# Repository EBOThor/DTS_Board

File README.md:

# DTS_Board
 Digital to Synchro board

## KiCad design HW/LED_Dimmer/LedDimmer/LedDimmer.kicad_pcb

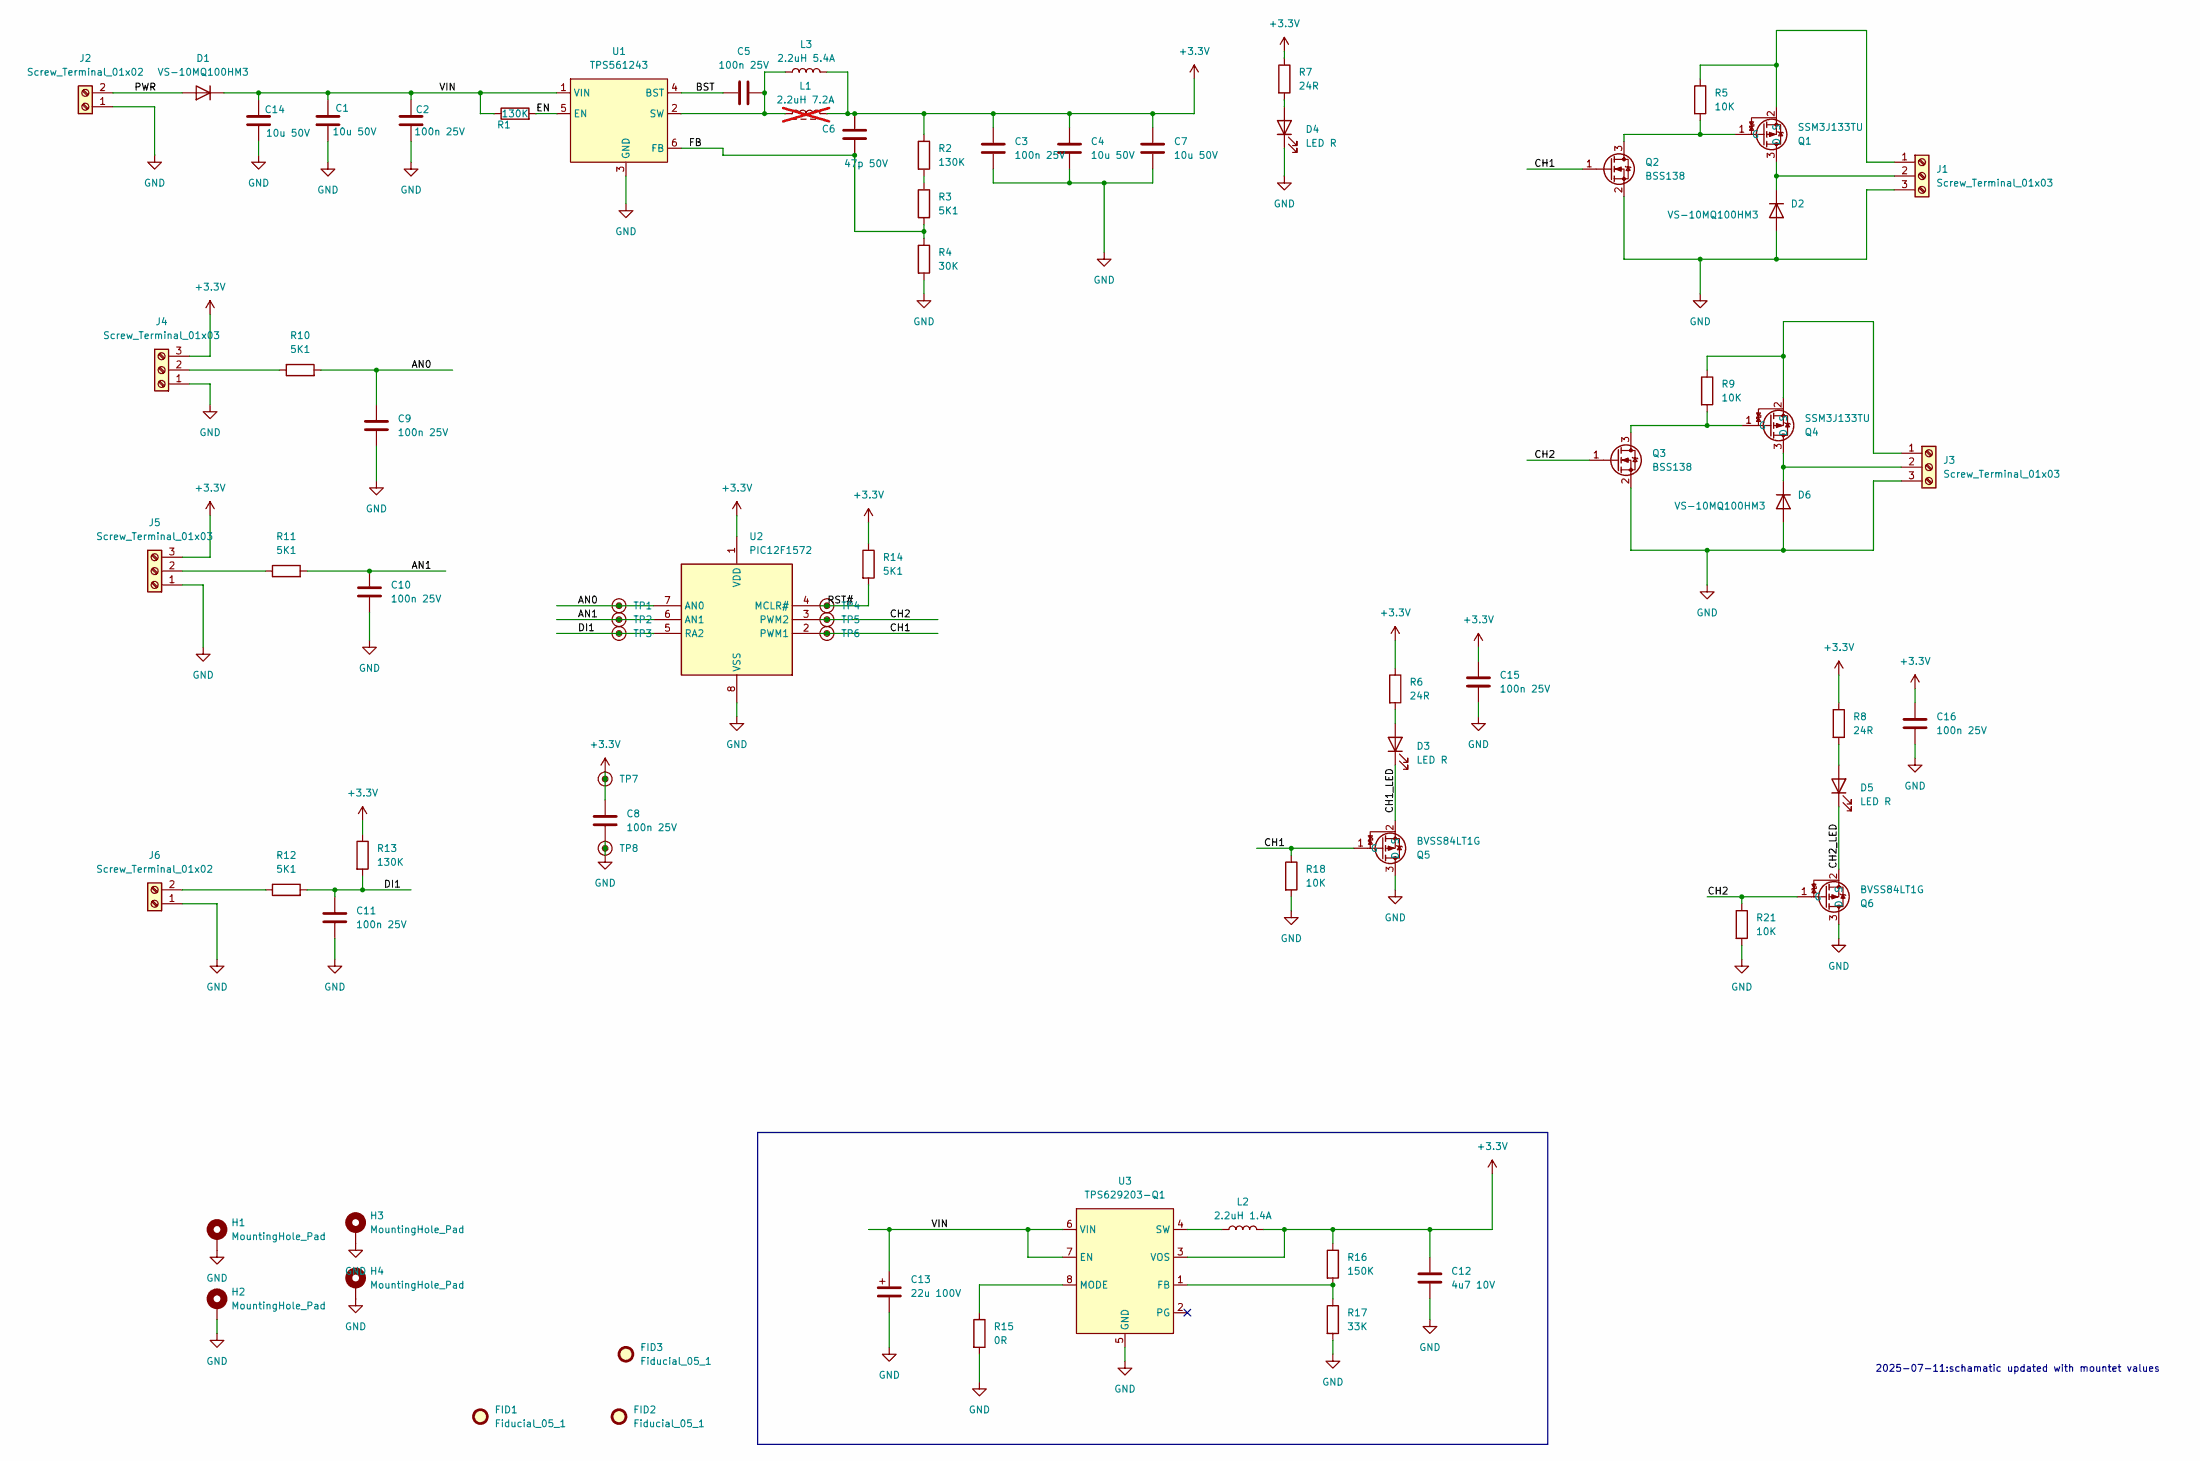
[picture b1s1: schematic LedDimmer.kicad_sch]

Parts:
C1, C14: 10u 50V; C_0805_2012Metric; MPN GRM21BR61H106KE43L
C2, C3, C5, C8, C9, C10, C11, C15, C16: 100n 25V; C_0603_1608Metric; MPN C;M;100n;10p;25V;S;0603
C4, C7: 10u 50V; C_0603_1608Metric; MPN C;M;10u;10p;50V;S;0603
C6: 47p 50V; C_0603_1608Metric; MPN C;C;T1;S;P0603;NA
C12: 4u7 10V; C_0603_1608Metric; MPN C;C;T1;S;P0603;NA
C13: 22u 100V; CP_Elec_8x10.5; MPN WE 865060853003
D1, D2, D6: VS-10MQ100HM3; D_SMA; MPN VS-10MQ100HM3/5AT
D3, D4, D5: LED R; LED_0603_1608Metric; MPN D;LED;R;3V;25mA
FID1, FID2, FID3: Fiducial_05_1; Fiducial_0.5mm_Mask1mm
H1, H2, H3, H4: MountingHole_Pad; MountingHole_2.2mm_M2_DIN965_Pad_TopBottom
J1, J3, J4, J5: Screw_Terminal_01x03; PinHeader_1x03_P2.54mm_Vertical
J2, J6: Screw_Terminal_01x02; PinHeader_1x02_P2.54mm_Vertical
L1: 2.2uH 7.2A; L_Bourns_bt_SRR1050HA; MPN SRR1050HA-2R2Y; not fitted
L2: 2.2uH 1.4A; L_0806_2016Metric; MPN DFE201612E-2R2M=P2
L3: 2.2uH 5.4A; L_1210_3225Metric; MPN IHLP1210BZEZ2R2M5A
Q1, Q4: SSM3J133TU; SOT-323_SC-70; MPN SSM3J133TU,LF
Q2, Q3: BSS138; SOT-23; MPN BSS138
Q5, Q6: BVSS84LT1G; SOT-23; MPN BVSS84LT1G
R1, R2, R13: 130K; R_0603_1608Metric; MPN R;G;T1;S;P0603;NA
R3, R10, R11, R12, R14: 5K1; R_0603_1608Metric; MPN R;G;5K1;S;P0603;NA
R4: 30K; R_0603_1608Metric; MPN R;G;T1;S;P0603;NA
R5, R9, R18, R21: 10K; R_0603_1608Metric; MPN R;G;10K;10P0;S;0603
R6, R7, R8: 24R; R_0603_1608Metric; MPN R;G;T1;S;P0603;NA
R15: 0R; R_0603_1608Metric; MPN R;G;0R;10P0;S;0603
R16: 150K; R_0603_1608Metric; MPN R;G;T1;S;P0603;NA
R17: 33K; R_0603_1608Metric; MPN R;G;T1;S;P0603;NA
TP1, TP2, TP3, TP4, TP5, TP6, TP7, TP8: TestPoint; TestPoint_THTPad_D1.0mm_Drill0.5mm
U1: TPS561243; SOT-563; MPN TPS561243DRLR
U2: PIC12F1572; SOIC-8_3.9x4.9mm_P1.27mm; MPN PIC12F1572-I/SN
U3: TPS629203-Q1; SOT-583-8; MPN TPS629203QDRLR

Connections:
+3.3V: C3.2, C4.1, C6.1, C7.1, C8.2, C12.1, C15.2, C16.2, J4.3, J5.3, L1.2, L2.2, L3.2, R2.1, R6.1, R7.1, R8.1, R13.1, R14.1, R16.1, TP7.1, U2.1 (VDD), U3.3 (VOS)
/AN0: C9.2, R10.2, TP1.1, U2.7 (AN0)
/AN1: C10.2, R11.2, TP2.1, U2.6 (AN1)
/BST: C5.1, U1.4 (BST)
/CH1: Q2.1 (G), Q5.1 (G), R18.1, TP6.1, U2.2 (PWM1)
/CH1_LED: D3.1 (K), Q5.2 (S)
/CH2: Q3.1 (G), Q6.1 (G), R21.1, TP5.1, U2.3 (PWM2)
/CH2_LED: D5.1 (K), Q6.2 (S)
/DI1: C11.2, R12.2, R13.2, TP3.1, U2.5 (RA2)
/EN: R1.2, U1.5 (EN)
/FB: C6.2, R3.2, R4.1, U1.6 (FB)
/PWR: D1.2 (A), J2.2
/RST#: R14.2, TP4.1, U2.4 (MCLR#)
/VIN: C1.1, C2.2, C13.1, C14.1, D1.1 (K), R1.1, U1.1 (VIN), U3.6 (VIN), U3.7 (EN)
GND: C1.2, C2.1, C3.1, C4.2, C7.2, C8.1, C9.1, C10.1, C11.1, C12.2, C13.2, C14.2, C15.1, C16.1, D2.2 (A), D4.1 (K), D6.2 (A), H1.1, H2.1, H3.1, H4.1, J1.3, J2.1, J3.3, J4.1, J5.1, J6.1, Q2.2 (S), Q3.2 (S), Q5.3 (D), Q6.3 (D), R4.2, R15.2, R17.2, R18.2, R21.2, TP8.1, U1.3 (GND), U2.8 (VSS), U3.5 (GND)
unnamed: D2.1 (K), J1.2, Q1.3 (D)
unnamed: D3.2 (A), R6.2
unnamed: D4.2 (A), R7.2
unnamed: D5.2 (A), R8.2
unnamed: D6.1 (K), J3.2, Q4.3 (D)
unnamed: J1.1, Q1.2 (S), R5.1
unnamed: J3.1, Q4.2 (S), R9.1
unnamed: J4.2, R10.1
unnamed: J5.2, R11.1
unnamed: J6.2, R12.1
unnamed: L2.1, U3.4 (SW)
unnamed: Q1.1 (G), Q2.3 (D), R5.2
unnamed: Q3.3 (D), Q4.1 (G), R9.2
unnamed: R2.2, R3.1
unnamed: R15.1, U3.8 (MODE)
unnamed: R16.2, R17.1, U3.1 (FB)
unnamed: C5.2, L1.1, L3.1, U1.2 (SW)

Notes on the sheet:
2025-07-11:schamatic updated with mountet values

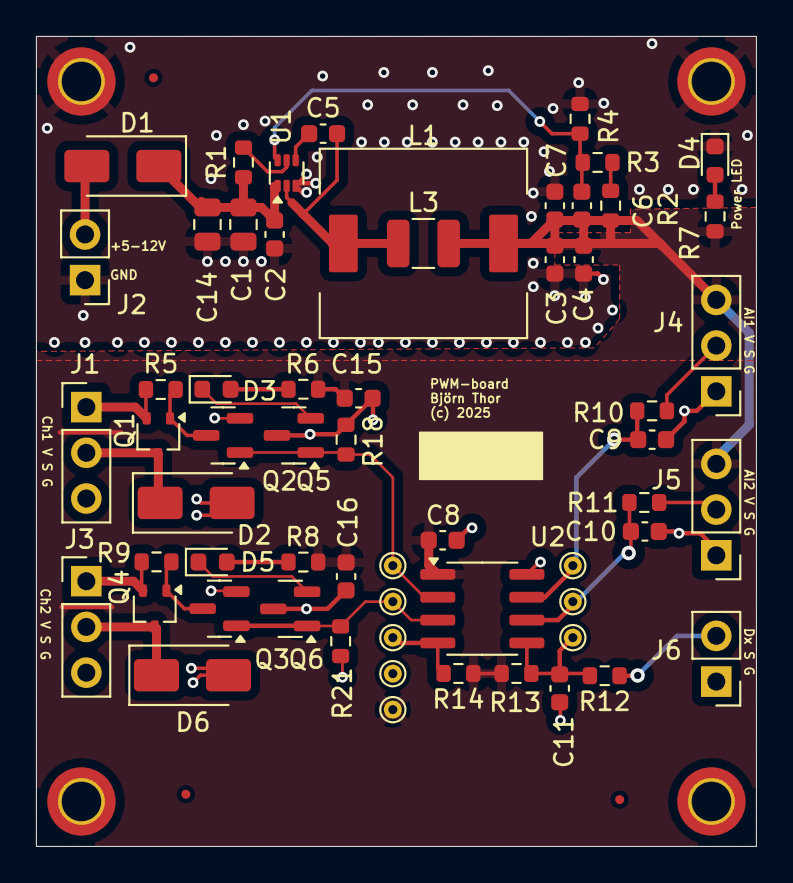
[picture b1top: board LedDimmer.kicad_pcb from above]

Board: 2 copper layers, 40.0 x 45.0 mm, 67 parts (0 on the bottom side), 29 nets.

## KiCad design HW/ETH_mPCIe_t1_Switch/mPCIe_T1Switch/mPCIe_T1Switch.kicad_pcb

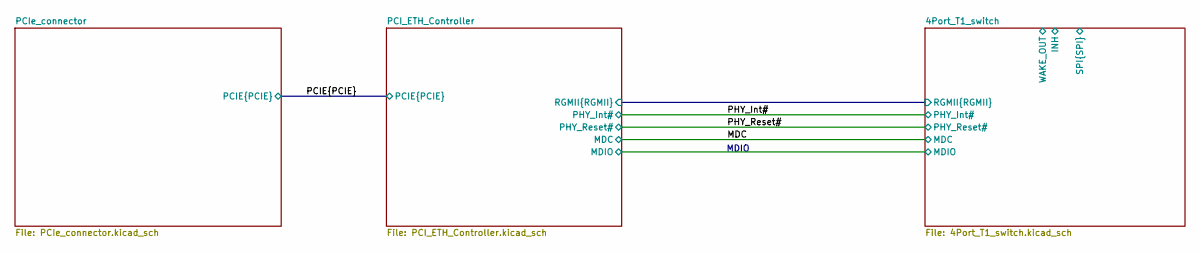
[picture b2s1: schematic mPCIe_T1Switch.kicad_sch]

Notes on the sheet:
MDIO

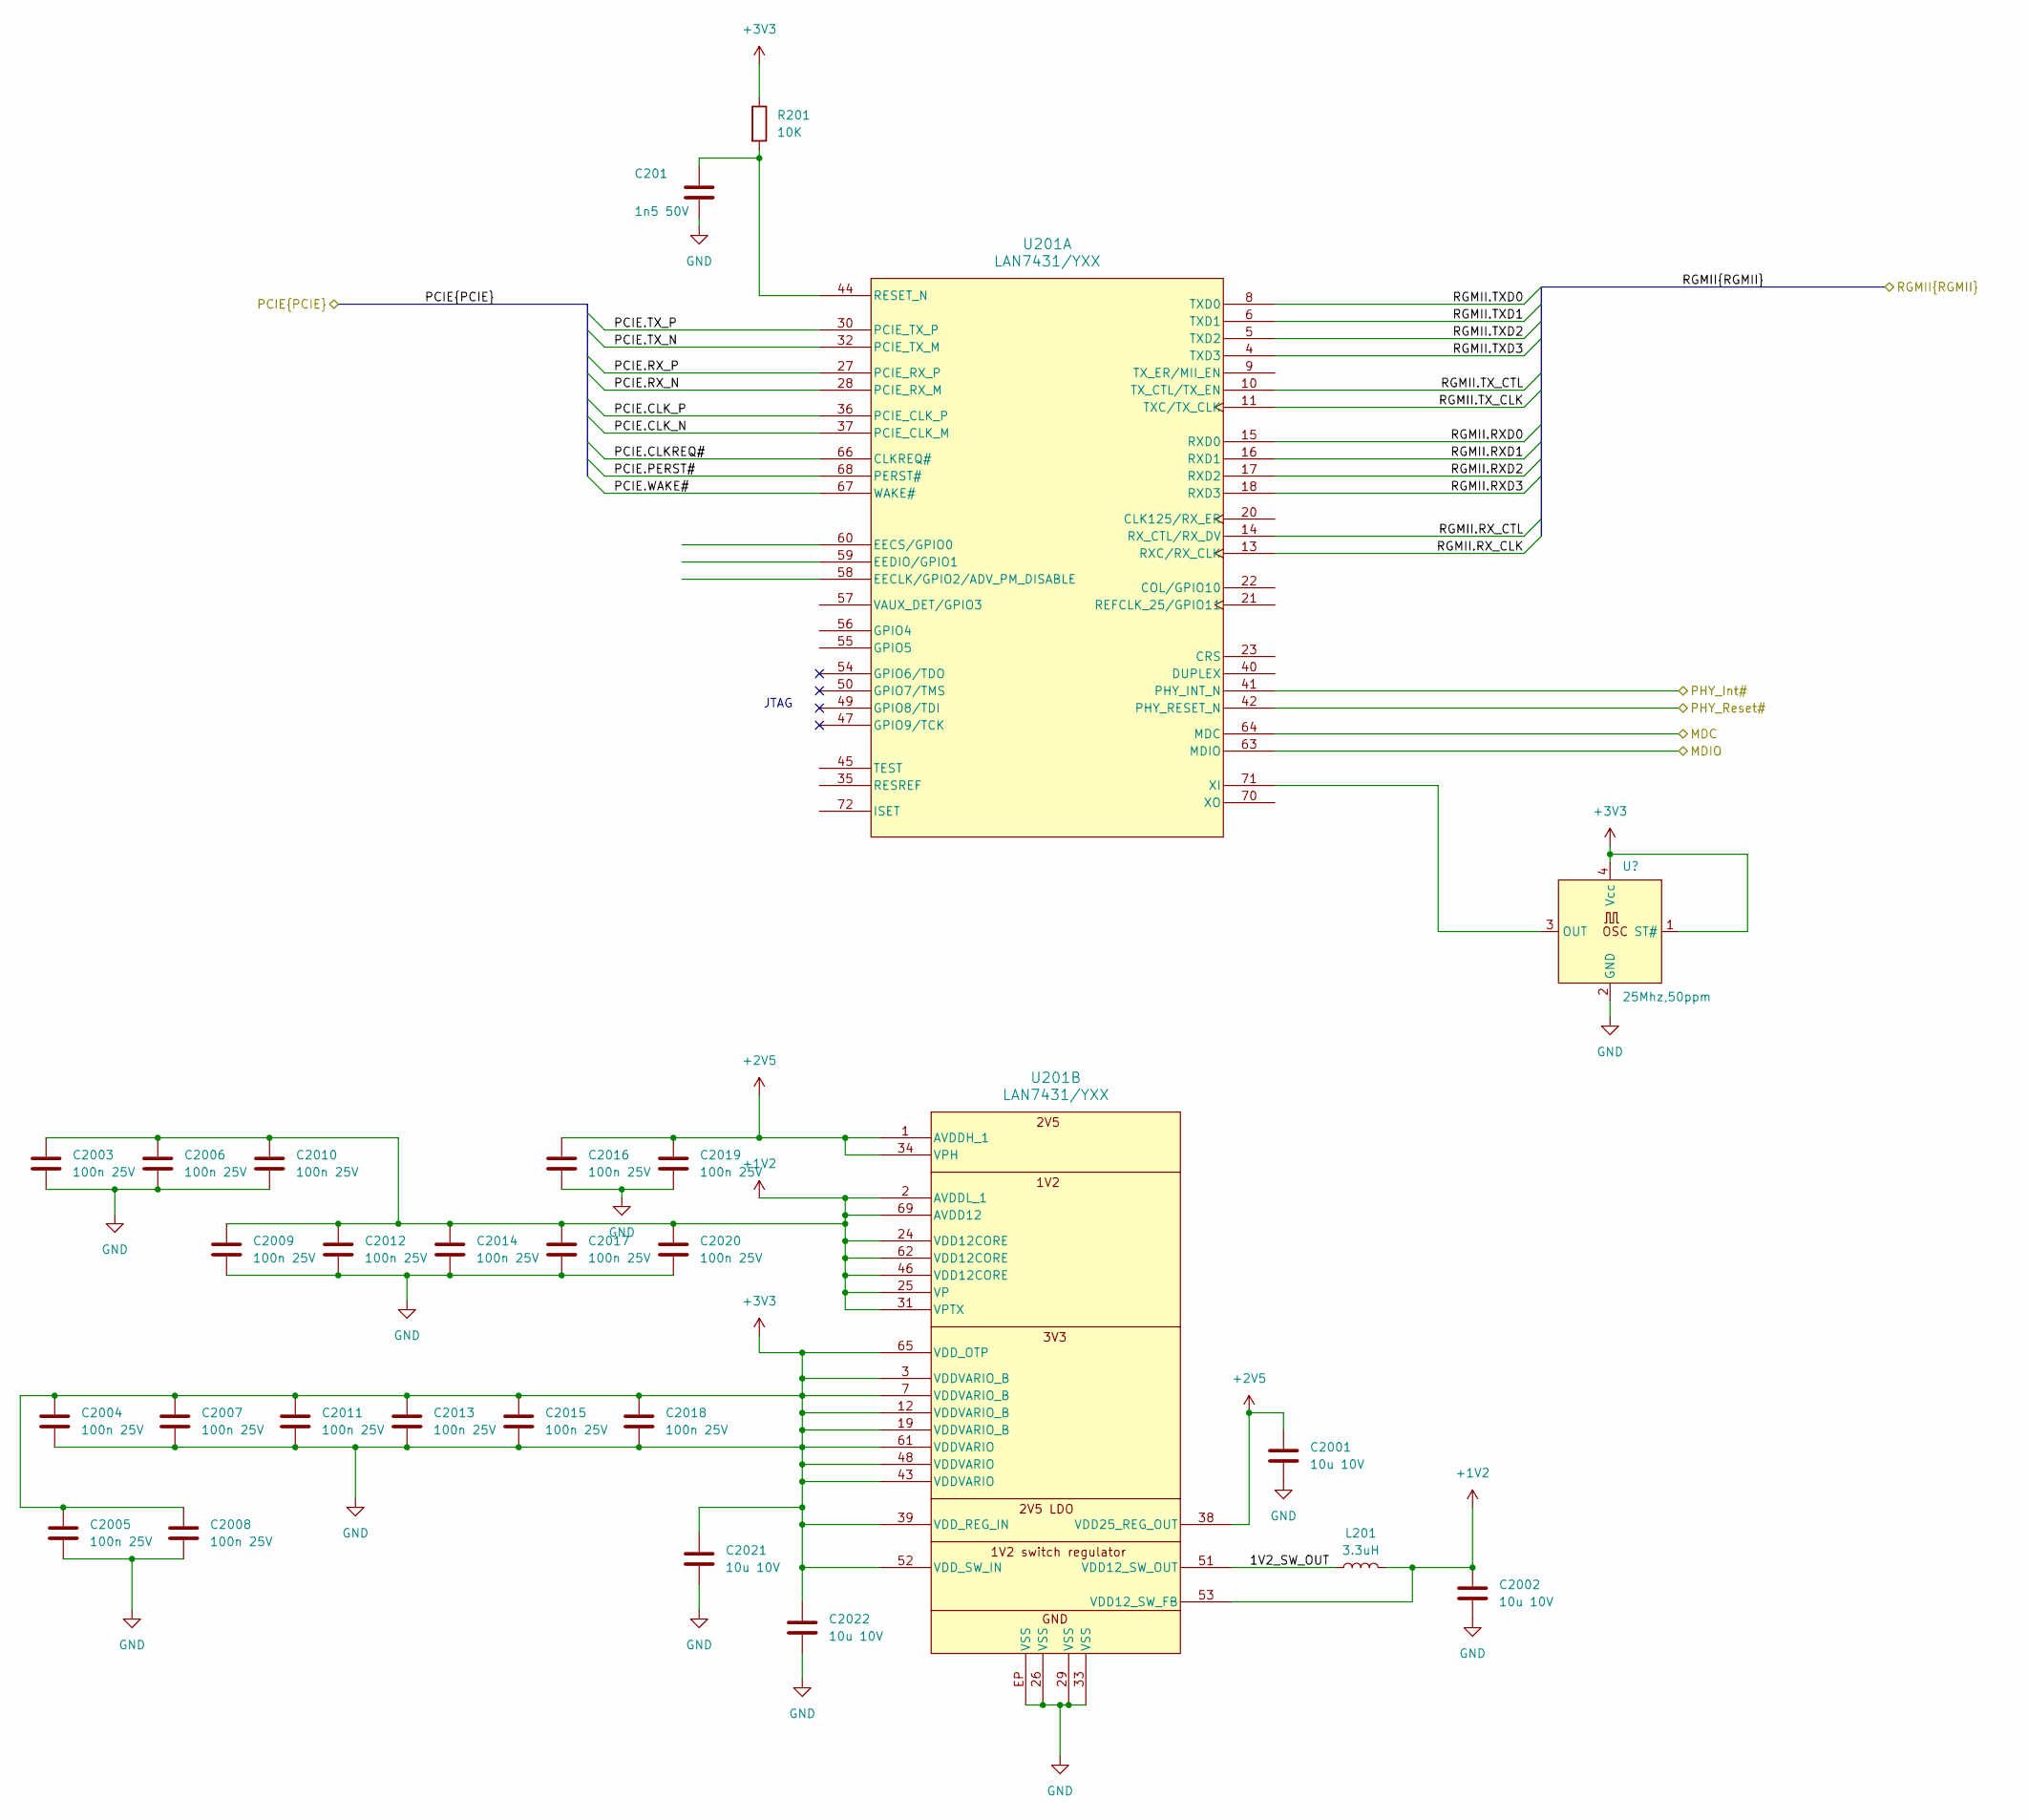
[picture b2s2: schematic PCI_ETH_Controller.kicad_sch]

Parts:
C201: 1n5 50V; C_0603_1608Metric; MPN C;C;T1;S;P0603;NA
C2001, C2002, C2021, C2022: 10u 10V; C_0603_1608Metric; MPN C;M;10u;10p;10V;S;0603
C2003, C2004, C2005, C2006, C2007, C2008, C2009, C2010, C2011, C2012, C2013, C2014, C2015, C2016, C2017, C2018, C2019, C2020: 100n 25V; C_0603_1608Metric; MPN C;M;100n;10p;25V;S;0603
L201: 3.3uH; L_0806_2016Metric; MPN SRP2010DPA-3R3M
R201: 10K; R_0603_1608Metric; MPN R;G;10K;10P0;S;0603
U201: LAN7431/YXX; SQFN72_YXX_MCH; MPN LAN7431

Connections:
+1V2: C2002.1, C2003.1, C2006.1, C2009.1, C2010.1, C2012.1, C2014.1, C2017.1, C2020.1, L201.2, U201.2 (AVDDL_1), U201.24 (VDD12CORE), U201.25 (VP), U201.31 (VPTX), U201.46 (VDD12CORE), U201.53 (VDD12_SW_FB), U201.62 (VDD12CORE), U201.69 (AVDD12)
+2V5: C2001.1, C2016.1, C2019.1, U201.1 (AVDDH_1), U201.34 (VPH), U201.38 (VDD25_REG_OUT)
+3V3: C201.2, C2001.2, C2002.2, C2003.2, C2004.1, C2004.2, C2005.1, C2005.2, C2006.2, C2007.1, C2007.2, C2008.1, C2008.2, C2009.2, C2010.2, C2011.1, C2011.2, C2012.2, C2013.1, C2013.2, C2014.2, C2015.1, C2015.2, C2016.2, C2017.2, C2018.1, C2018.2, C2019.2, C2020.2, C2021.1, C2021.2, C2022.1, C2022.2, R201.1, U201.3 (VDDVARIO_B), U201.7 (VDDVARIO_B), U201.12 (VDDVARIO_B), U201.19 (VDDVARIO_B), U201.26 (VSS), U201.29 (VSS), U201.33 (VSS), U201.39 (VDD_REG_IN), U201.43 (VDDVARIO), U201.48 (VDDVARIO), U201.52 (VDD_SW_IN), U201.61 (VDDVARIO), U201.65 (VDD_OTP), U201.EP (VSS); also elsewhere on the board
/4Port_T1_switch/MDIO: U201.63 (MDIO); also elsewhere on the board
/4Port_T1_switch/RGMII.RXD0: U201.15 (RXD0); also elsewhere on the board
/4Port_T1_switch/RGMII.RXD1: U201.16 (RXD1); also elsewhere on the board
/4Port_T1_switch/RGMII.RXD2: U201.17 (RXD2); also elsewhere on the board
/4Port_T1_switch/RGMII.RXD3: U201.18 (RXD3); also elsewhere on the board
/4Port_T1_switch/RGMII.RX_CLK: U201.13 (RXC/RX_CLK); also elsewhere on the board
/4Port_T1_switch/RGMII.RX_CTL: U201.14 (RX_CTL/RX_DV); also elsewhere on the board
/4Port_T1_switch/RGMII.TXD0: U201.8 (TXD0); also elsewhere on the board
/4Port_T1_switch/RGMII.TXD1: U201.6 (TXD1); also elsewhere on the board
/4Port_T1_switch/RGMII.TXD2: U201.5 (TXD2); also elsewhere on the board
/4Port_T1_switch/RGMII.TXD3: U201.4 (TXD3); also elsewhere on the board
/4Port_T1_switch/RGMII.TX_CLK: U201.11 (TXC/TX_CLK); also elsewhere on the board
/4Port_T1_switch/RGMII.TX_CTL: U201.10 (TX_CTL/TX_EN); also elsewhere on the board
/MDC: U201.64 (MDC); also elsewhere on the board
/PCIE.CLKREQ#: U201.66 (CLKREQ#); also elsewhere on the board
/PCIE.CLK_N: U201.37 (PCIE_CLK_M); also elsewhere on the board
/PCIE.CLK_P: U201.36 (PCIE_CLK_P); also elsewhere on the board
/PCIE.PERST#: U201.68 (PERST#); also elsewhere on the board
/PCIE.RX_N: U201.28 (PCIE_RX_M); also elsewhere on the board
/PCIE.RX_P: U201.27 (PCIE_RX_P); also elsewhere on the board
/PCIE.TX_N: U201.32 (PCIE_TX_M); also elsewhere on the board
/PCIE.TX_P: U201.30 (PCIE_TX_P); also elsewhere on the board
/PCIE.WAKE#: U201.67 (WAKE#); also elsewhere on the board
/PCI_ETH_Controller/1V2_SW_OUT: L201.1, U201.51 (VDD12_SW_OUT)
/PHY_Int#: U201.41 (PHY_INT_N); also elsewhere on the board
/PHY_Reset#: U201.42 (PHY_RESET_N); also elsewhere on the board
unnamed: C201.1, R201.2, U201.44 (RESET_N)

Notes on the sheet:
JTAG

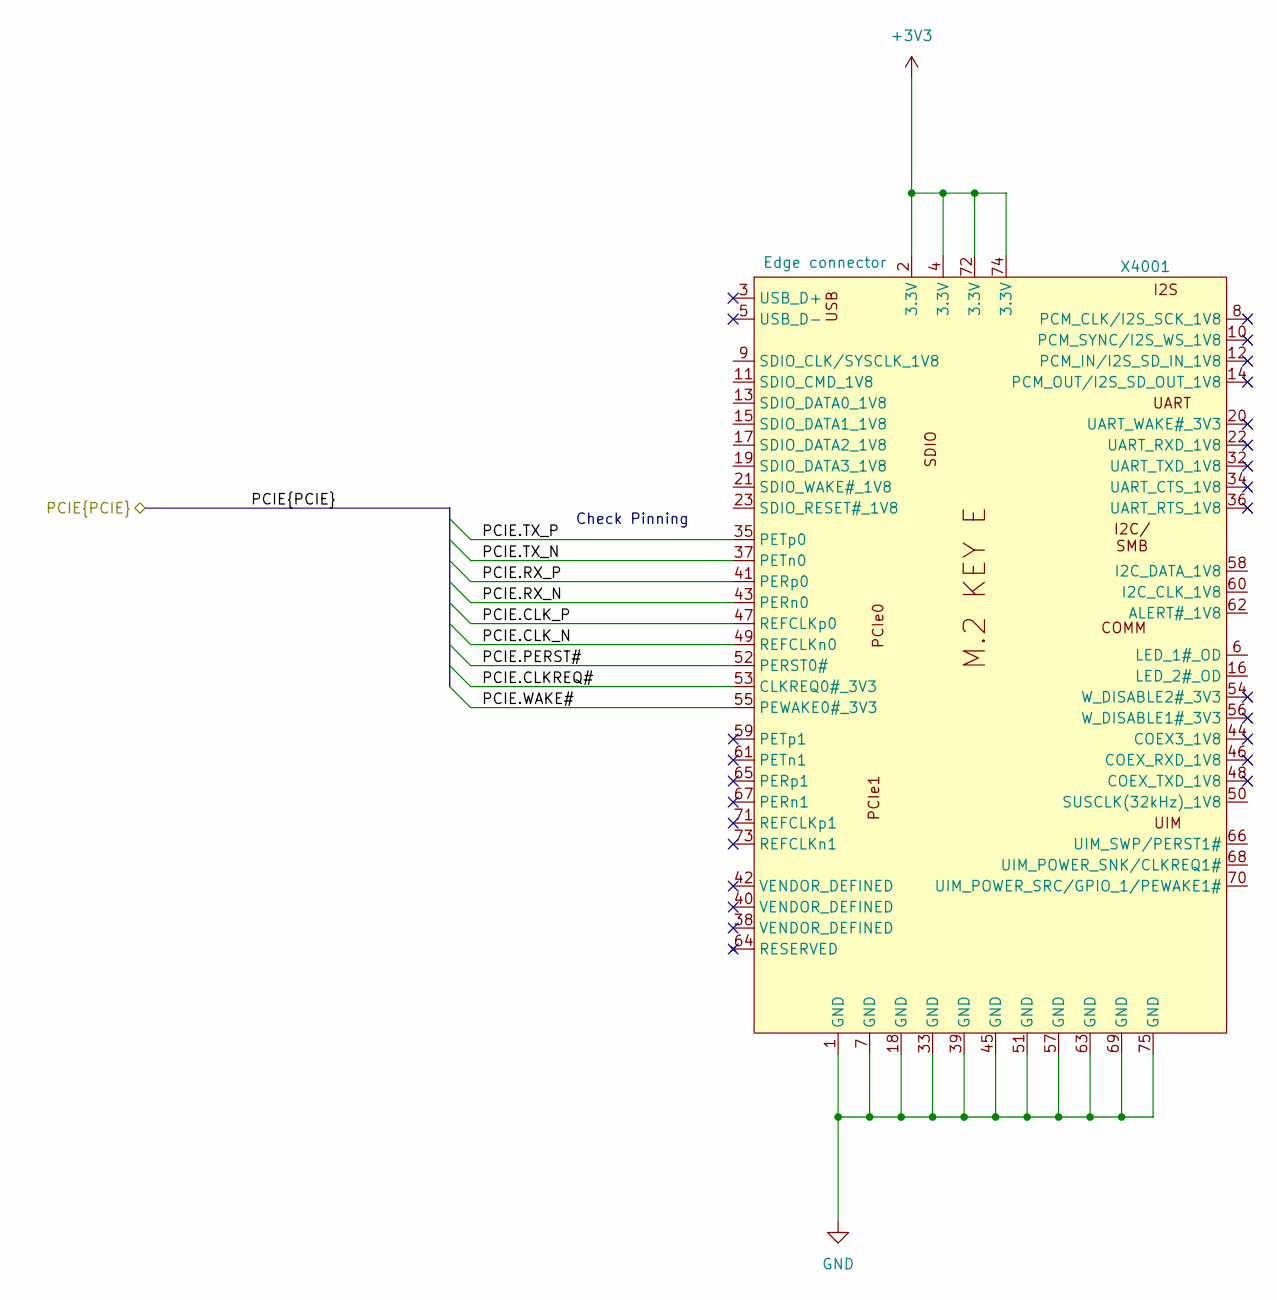
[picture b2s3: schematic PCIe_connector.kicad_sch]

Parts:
X4001: M.2_KEY_E

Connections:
+3V3: X4001.1 (GND), X4001.2 (3.3V), X4001.4 (3.3V), X4001.7 (GND), X4001.18 (GND), X4001.33 (GND), X4001.39 (GND), X4001.45 (GND), X4001.51 (GND), X4001.57 (GND), X4001.63 (GND), X4001.69 (GND), X4001.72 (3.3V), X4001.74 (3.3V), X4001.75 (GND); also elsewhere on the board
/PCIE.CLKREQ#: X4001.53 (CLKREQ0#_3V3); also elsewhere on the board
/PCIE.CLK_N: X4001.49 (REFCLKn0); also elsewhere on the board
/PCIE.CLK_P: X4001.47 (REFCLKp0); also elsewhere on the board
/PCIE.PERST#: X4001.52 (PERST0#); also elsewhere on the board
/PCIE.RX_N: X4001.43 (PERn0); also elsewhere on the board
/PCIE.RX_P: X4001.41 (PERp0); also elsewhere on the board
/PCIE.TX_N: X4001.37 (PETn0); also elsewhere on the board
/PCIE.TX_P: X4001.35 (PETp0); also elsewhere on the board
/PCIE.WAKE#: X4001.55 (PEWAKE0#_3V3); also elsewhere on the board

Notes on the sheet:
Check Pinning

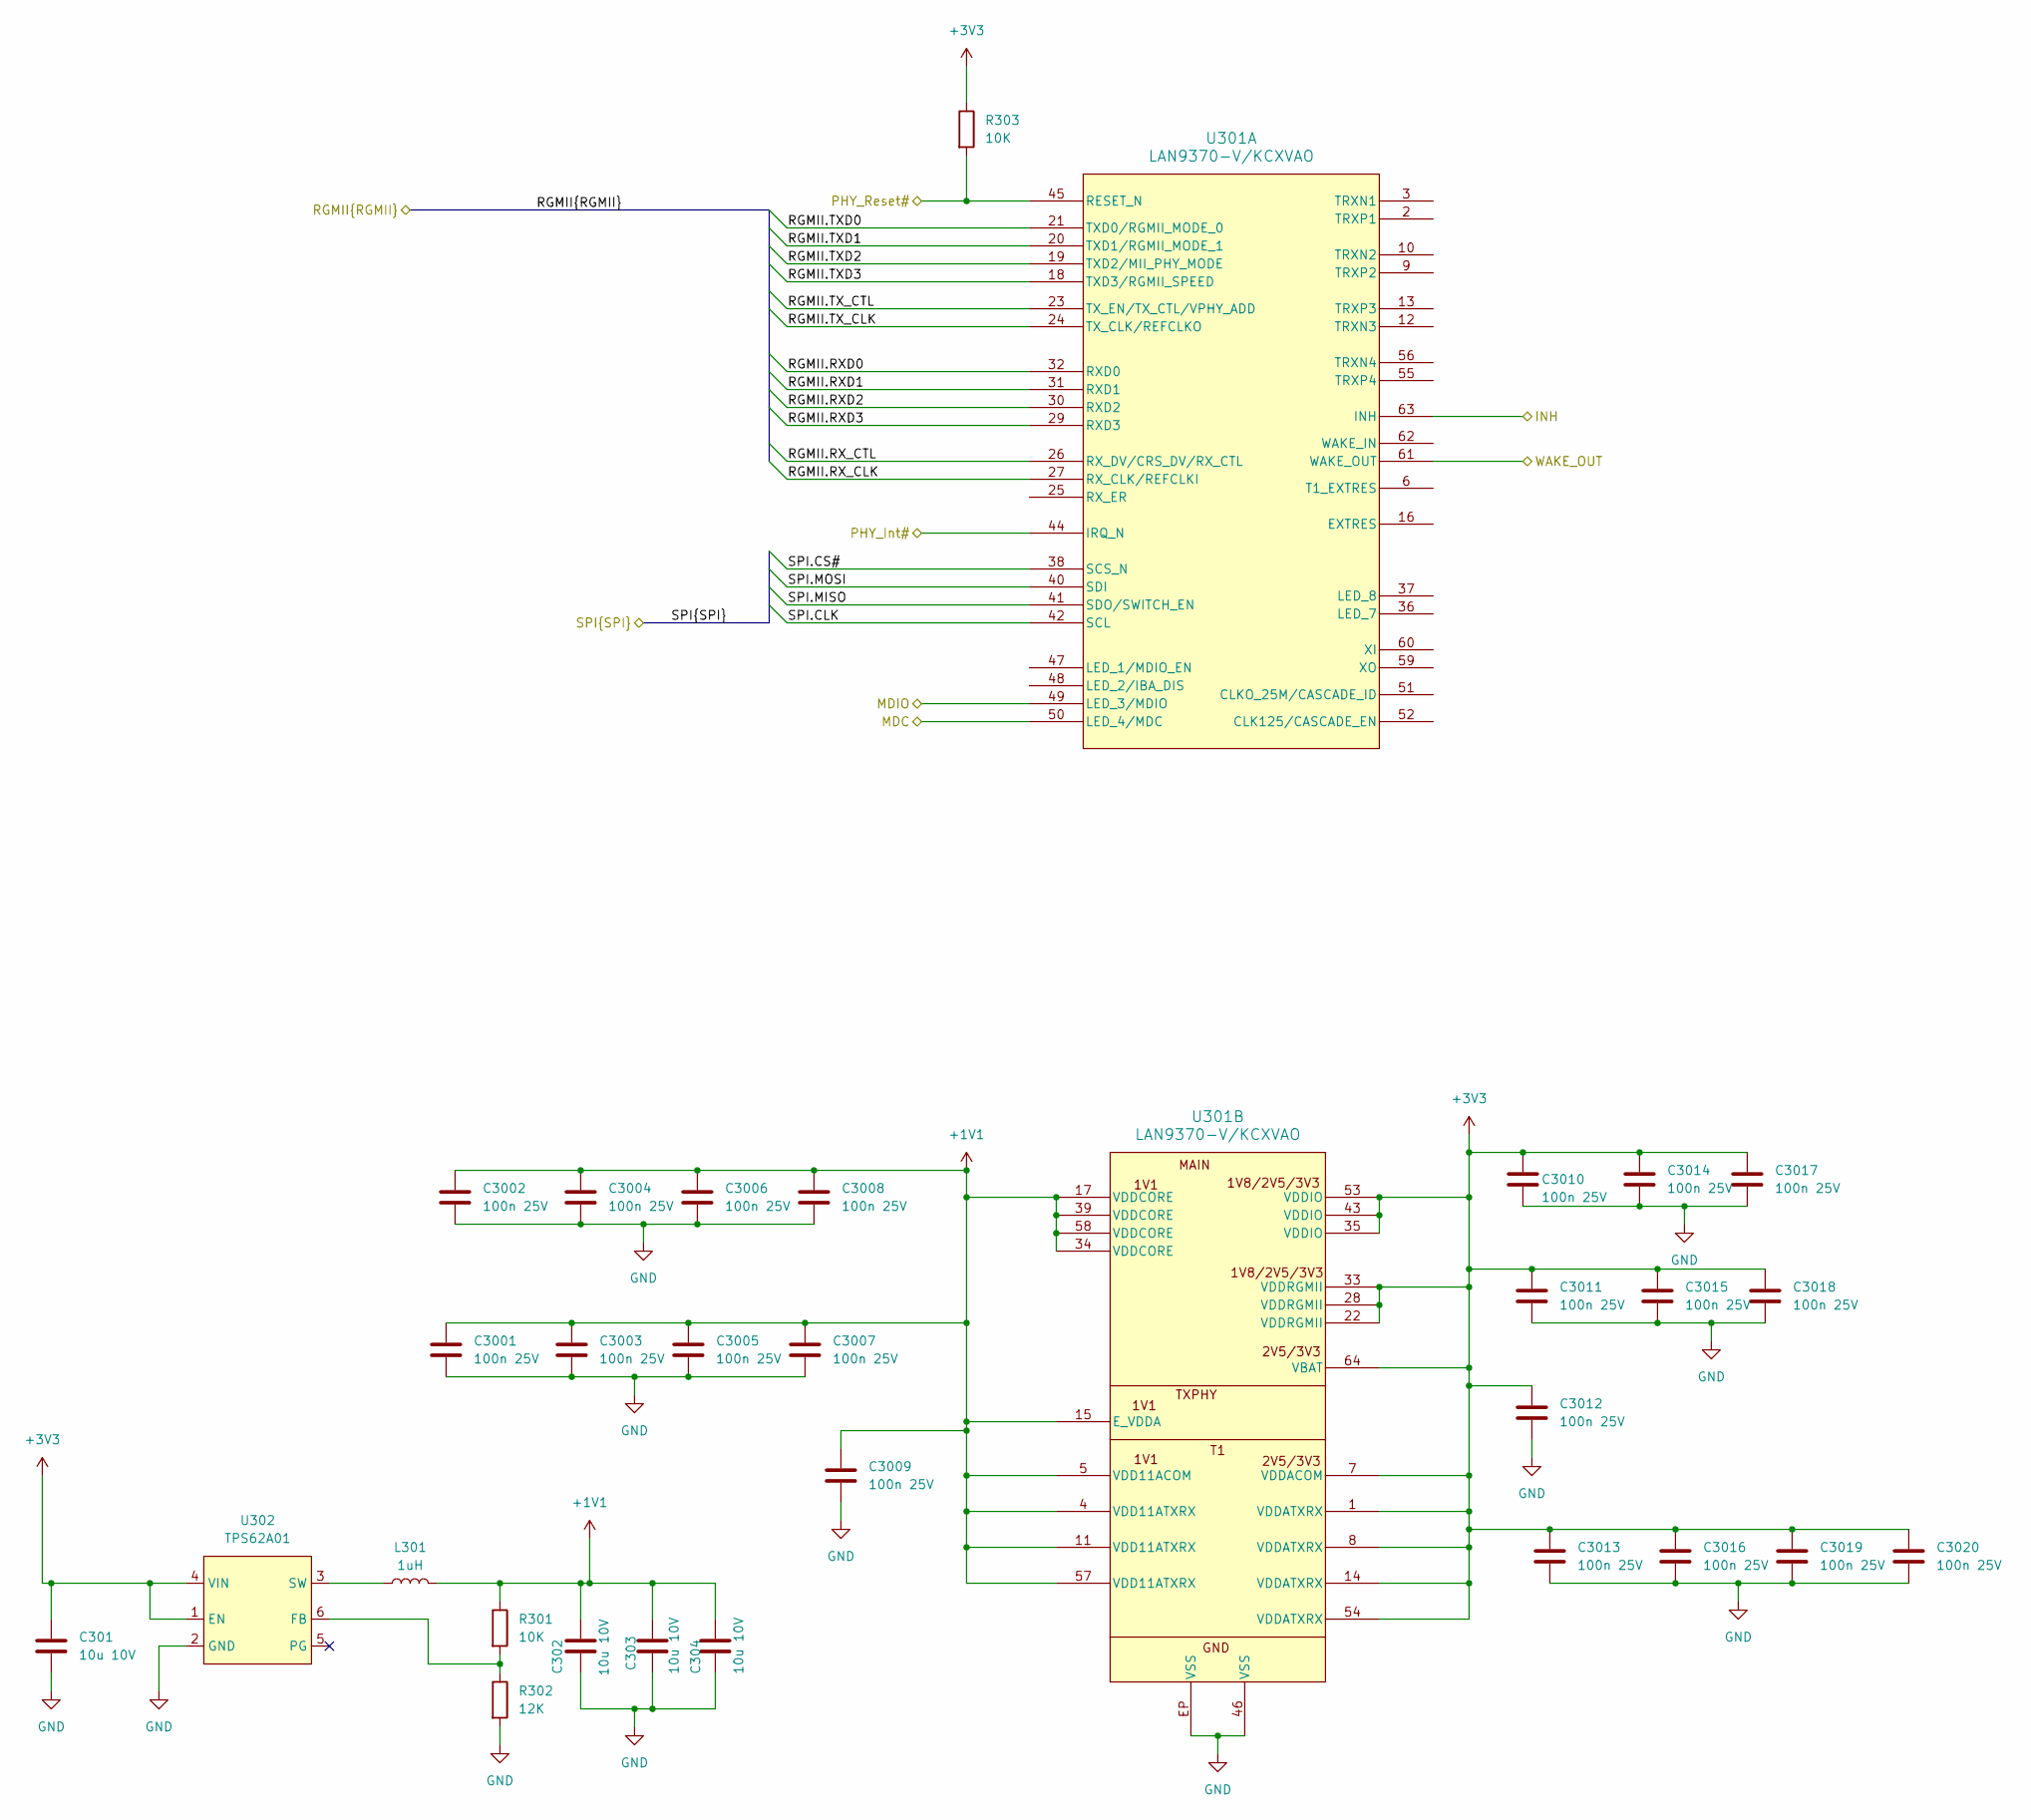
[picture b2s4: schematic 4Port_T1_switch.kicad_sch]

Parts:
C301, C302, C303, C304: 10u 10V; C_0603_1608Metric; MPN C;M;10u;10p;10V;S;0603
C3001, C3002, C3003, C3004, C3005, C3006, C3007, C3008, C3009, C3010, C3011, C3012, C3013, C3014, C3015, C3016, C3017, C3018, C3019, C3020: 100n 25V; C_0603_1608Metric; MPN C;M;100n;10p;25V;S;0603
L301: 1uH; L_0805_2012Metric; MPN CIGT201208EH1R0MNE
R301, R303: 10K; R_0603_1608Metric; MPN R;G;10K;10P0;S;0603
R302: 12K; R_0603_1608Metric; MPN R;G;T1;S;P0603;NA
U301: LAN9370-V/KCXVAO; VQFN64_KCX_6.5X6.5EPAD_MCH; MPN LAN9370
U302: TPS62A01; SOT-23-6; MPN TPS62A01

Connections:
+1V1: C302.1, C303.1, C304.1, C3001.1, C3002.1, C3003.1, C3004.1, C3005.1, C3006.1, C3007.1, C3008.1, C3009.1, L301.2, R301.1, U301.4 (VDD11ATXRX), U301.5 (VDD11ACOM), U301.11 (VDD11ATXRX), U301.15 (E_VDDA), U301.17 (VDDCORE), U301.34 (VDDCORE), U301.39 (VDDCORE), U301.57 (VDD11ATXRX), U301.58 (VDDCORE)
+3V3: C301.1, C301.2, C302.2, C303.2, C304.2, C3001.2, C3002.2, C3003.2, C3004.2, C3005.2, C3006.2, C3007.2, C3008.2, C3009.2, C3010.1, C3010.2, C3011.1, C3011.2, C3012.1, C3012.2, C3013.1, C3013.2, C3014.1, C3014.2, C3015.1, C3015.2, C3016.1, C3016.2, C3017.1, C3017.2, C3018.1, C3018.2, C3019.1, C3019.2, C3020.1, C3020.2, R302.2, R303.1, U301.1 (VDDATXRX), U301.7 (VDDACOM), U301.8 (VDDATXRX), U301.14 (VDDATXRX), U301.22 (VDDRGMII), U301.28 (VDDRGMII), U301.33 (VDDRGMII), U301.35 (VDDIO), U301.43 (VDDIO), U301.46 (VSS), U301.53 (VDDIO), U301.54 (VDDATXRX), U301.64 (VBAT), U301.EP (VSS), U302.1 (EN), U302.2 (GND), U302.4 (VIN); also elsewhere on the board
/4Port_T1_switch/INH: U301.63 (INH)
/4Port_T1_switch/MDIO: U301.49 (LED_3/MDIO); also elsewhere on the board
/4Port_T1_switch/RGMII.RXD0: U301.32 (RXD0); also elsewhere on the board
/4Port_T1_switch/RGMII.RXD1: U301.31 (RXD1); also elsewhere on the board
/4Port_T1_switch/RGMII.RXD2: U301.30 (RXD2); also elsewhere on the board
/4Port_T1_switch/RGMII.RXD3: U301.29 (RXD3); also elsewhere on the board
/4Port_T1_switch/RGMII.RX_CLK: U301.27 (RX_CLK/REFCLKI); also elsewhere on the board
/4Port_T1_switch/RGMII.RX_CTL: U301.26 (RX_DV/CRS_DV/RX_CTL); also elsewhere on the board
/4Port_T1_switch/RGMII.TXD0: U301.21 (TXD0/RGMII_MODE_0); also elsewhere on the board
/4Port_T1_switch/RGMII.TXD1: U301.20 (TXD1/RGMII_MODE_1); also elsewhere on the board
/4Port_T1_switch/RGMII.TXD2: U301.19 (TXD2/MII_PHY_MODE); also elsewhere on the board
/4Port_T1_switch/RGMII.TXD3: U301.18 (TXD3/RGMII_SPEED); also elsewhere on the board
/4Port_T1_switch/RGMII.TX_CLK: U301.24 (TX_CLK/REFCLKO); also elsewhere on the board
/4Port_T1_switch/RGMII.TX_CTL: U301.23 (TX_EN/TX_CTL/VPHY_ADD); also elsewhere on the board
/4Port_T1_switch/SPI.CLK: U301.42 (SCL)
/4Port_T1_switch/SPI.CS#: U301.38 (SCS_N)
/4Port_T1_switch/SPI.MISO: U301.41 (SDO/SWITCH_EN)
/4Port_T1_switch/SPI.MOSI: U301.40 (SDI)
/4Port_T1_switch/WAKE_OUT: U301.61 (WAKE_OUT)
/MDC: U301.50 (LED_4/MDC); also elsewhere on the board
/PHY_Int#: U301.44 (IRQ_N); also elsewhere on the board
/PHY_Reset#: R303.2, U301.45 (RESET_N); also elsewhere on the board
unnamed: R301.2, R302.1, U302.6 (FB)
unnamed: L301.1, U302.3 (SW)

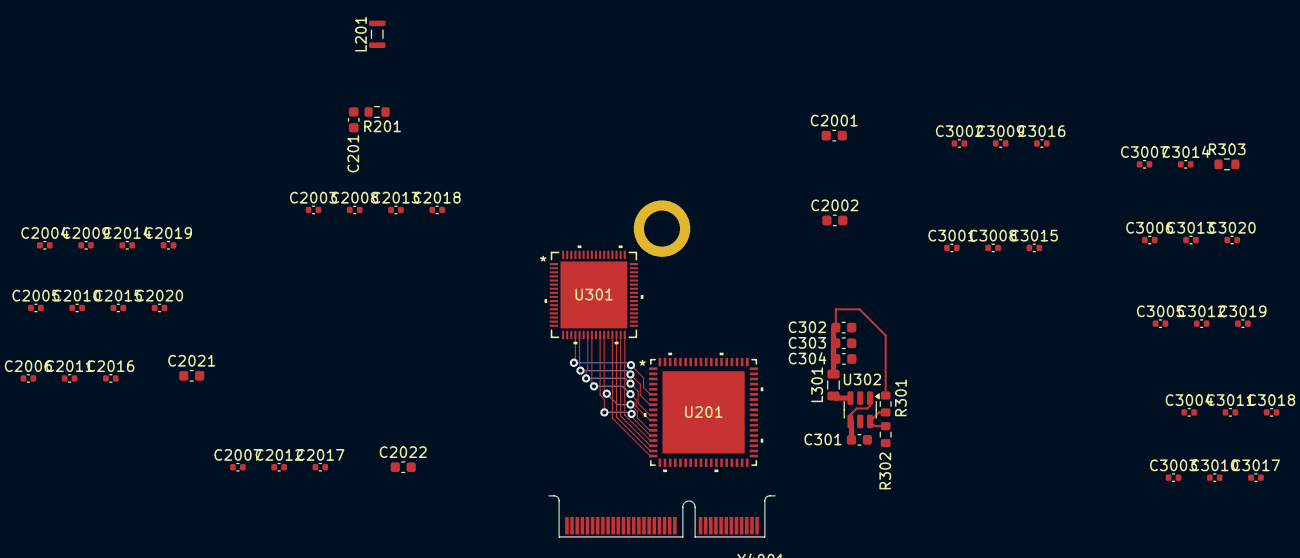
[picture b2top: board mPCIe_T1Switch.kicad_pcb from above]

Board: 4 copper layers, 57 parts (0 on the bottom side), 33 nets.

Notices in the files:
HW/DTS_Board/DTS_Board.kicad_pcb:
Björn Thor (c) 2023
(c) 2023
HW/LED_Dimmer/LedDimmer/LedDimmer.kicad_pcb:
(c) 2025
